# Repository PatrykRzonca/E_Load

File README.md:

# E_Load
This is a directory for E_Load project created in Kicad.

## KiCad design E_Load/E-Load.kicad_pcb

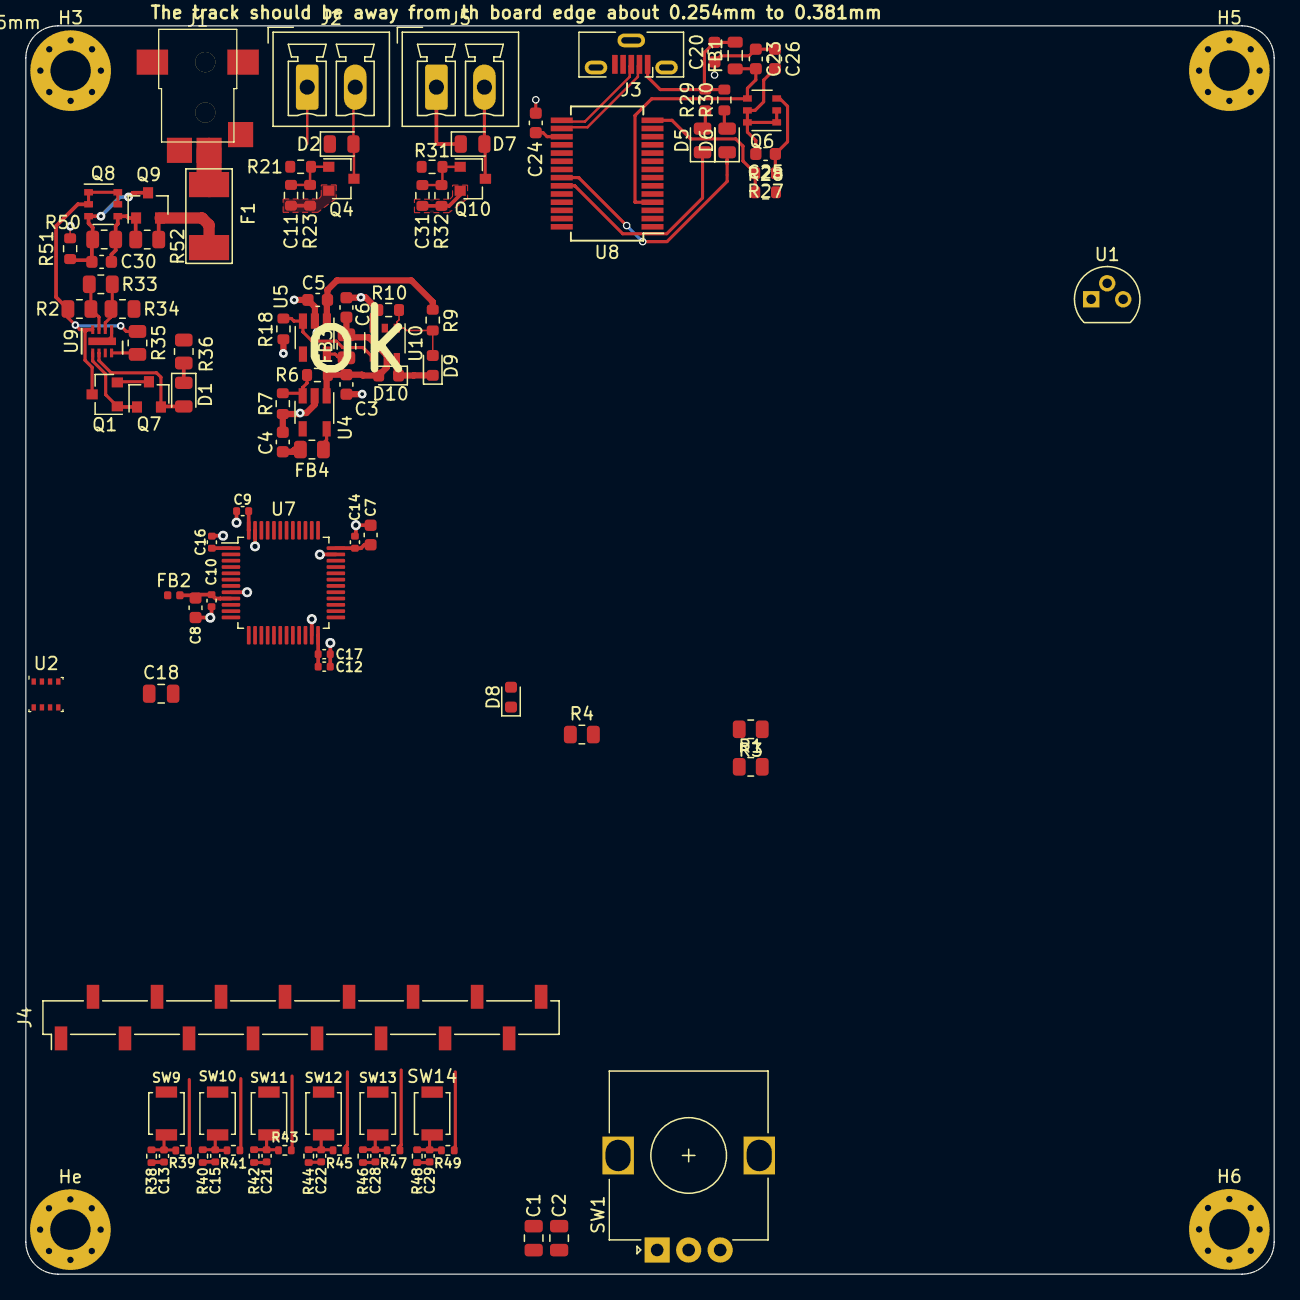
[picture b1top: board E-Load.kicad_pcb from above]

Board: 2 copper layers, 99.1 x 99.1 mm, 109 parts (0 on the bottom side), 49 nets.

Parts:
C1, C2, C18: 100n; C_0805_2012Metric
C3, C4, C5, C6, C30: C; C_0603_1608Metric
C7: 4u7; C_0603_1608Metric
C8: 1u; C_0603_1608Metric
C9, C10, C12, C14, C16, C17: 100n; C_0402_1005Metric
C11, C31: 100n; R_0603_1608Metric
C13, C15, C21, C22, C28, C29: C; C_0402_1005Metric
C20, C23, C24, C25, C26: 100n; C_0603_1608Metric
D1: LED; LED_0805_2012Metric
D2, D7: D; D_0805_2012Metric
D5: RED; LED_0805_2012Metric
D6: BLUE; LED_0805_2012Metric
D8, D9, D10: D_Schottky; D_0603_1608Metric
F1: Fuse; 0680-0500-12 BEL FUSE
FB1: Ferrite_Bead; L_0805_2012Metric
FB2: Ferrite_Bead_Small; L_0402_1005Metric
FB3, FB4: Ferrite_Bead_Small; R_0805_2012Metric
H3, H5, H6: MountingHole_Pad; MountingHole_3.2mm_M3_Pad_Via
He: MountingHole_Pad; MountingHole_3.2mm_M3_Pad_Via
J1: DC-8S_1.3mm_Pin; SMD DC SOCKETS DC-8S 1.3mm Pin
J2, J5: Screw_Terminal_01x02; PhoenixContact_MCV_1,5_2-G-3.81_1x02_P3.81mm_Vertical
J3: USB_B; USB_Micro-B_Molex-105133-0001
J4: Conn_01x16; PinSocket_1x16_P2.54mm_Vertical_SMD_Pin1Left
Q1, Q7: DMN24H3D5L; SOT-23
Q4, Q10: 2N7002E; SOT-23
Q6, Q8: PMN48XP; TSOP-6_1.65x3.05mm_P0.95mm
Q9: BC807; SOT-23
R1, R3, R4: 10k; R_0805_2012Metric
R2, R33, R34, R35, R36, R50, R52: R; R_0805_2012Metric
R6, R7, R18, R51: R; R_0603_1608Metric
R9, R10, R21, R23, R27, R28, R30, R31, R32: 10k; R_0603_1608Metric
R29: 10kΩ; R_0603_1608Metric
R38, R39, R40, R41, R42, R43, R44, R45, R46, R47, R48, R49: 10k; R_0402_1005Metric
SW1: Rotary_Encoder_Switch; RotaryEncoder_Alps_EC12E_Vertical_H20mm
SW9, SW10, SW11, SW12, SW13, SW14: SW_Push; SW_SPST_B3U-1000P
U1: DS18B20; TO-92
U2: BME280; Bosch_LGA-8_2.5x2.5mm_P0.65mm_ClockwisePinNumbering
U4: NCP718xSN330; TSOT-23-5
U5: NCP718xSN500; TSOT-23-5
U7: STM32F103C8Tx; LQFP-48_7x7mm_P0.5mm
U8: FT232RL; SSOP-28_5.3x10.2mm_P0.65mm
U9: LTC4365DDB; DFN-8-1EP_2x3mm_P0.5mm_EP0.61x2.2mm
U10: 74AHC1G86; TSOP-5_1.65x3.05mm_P0.95mm

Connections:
3V3_PS: C4.2, FB4.2, R1.2, R3.2, R4.2, U2.6, U2.8
5V_PS: C3.2, C6.2, D8.1, D10.2, FB3.2, J4.2, J4.15, R6.2, U1.3, U4.1
+3V3: C24.2, U8.17
+5V: C20.2, FB1.2, J3.1, R29.2, R30.2
/5V_USB: C25.2, C26.2, D8.2, Q6.1, Q6.2, Q6.5, Q6.6, U10.2
/CBUS3: R27.2, R28.1, U8.14
/D+: J3.3, U8.15
/D-: J3.2, U8.16
/ENC_BUTTON_A: C2.2, R3.1, SW1.A
/ENC_BUTTON_B: C1.2, R1.1, SW1.B
/LDO_5V_EN: R18.2, U5.3, U10.4
/~FAULT: U7.18, U9.7
GND: C1.1, C2.1, C3.1, C4.1, C5.1, C6.1, C7.1, C8.1, C9.1, C10.1, C11.1, C12.1, C13.2, C14.1, C15.2, C16.1, C17.1, C18.1, C20.1, C21.2, C22.2, C23.1, C24.1, C26.1, C28.2, C29.2, C31.1, H3.1, H5.1, H6.1, He.1, J1.2, J3.4, J3.5, J4.1, J4.16, Q4.2, Q10.2, R7.1, R10.1, R18.1, R23.2, R32.2, R34.1, R36.2, R38.1, R40.1, R42.1, R44.1, R46.2, R48.1, R51.1, SW1.C, U1.1, U2.1, U2.7, U4.2, U5.2, U7.8, U7.23, U7.35, U7.47, U8.7, U8.18, U8.21, U8.25, U8.26, U9.1, U9.9, U10.3
Main_PS: C5.2, D1.2, D2.1, D7.1, J2.1, J5.1, Q7.2, R9.2, U5.1, U9.6
unnamed: C11.2, Q4.1, R21.2, R23.1
unnamed: C13.1, R38.2, R39.1, SW9.1
unnamed: C15.1, R40.2, R41.1, SW10.1
unnamed: C18.2, U7.7
unnamed: C21.1, R42.2, R43.1, SW11.1
unnamed: C22.1, R44.2, R45.1, SW12.1
unnamed: C23.2, FB1.1, Q6.4, U8.4, U8.20
unnamed: C25.1, Q6.3, R27.1
unnamed: C28.1, R46.1, R47.1, SW13.1
unnamed: C29.1, R48.2, R49.1, SW14.1
unnamed: C30.1, Q8.3, Q9.3, R50.1, R51.2
unnamed: C30.2, Q8.4, Q9.1, R50.2, R52.2
unnamed: C31.2, Q10.1, R31.2, R32.1
unnamed: D1.1, R36.1
unnamed: D2.2, J2.2, Q4.3
unnamed: D5.1, U8.23
unnamed: D5.2, R29.1
unnamed: D6.1, U8.22
unnamed: D6.2, R30.1
unnamed: D7.2, J5.2, Q10.3
unnamed: D9.2, R9.1, R10.2, U10.1
unnamed: F1.1, Q9.2, R52.1
unnamed: F1.2, J1.1
unnamed: FB3.1, U5.5
unnamed: FB4.1, U4.5
unnamed: Q1.1, Q7.1, U9.5
unnamed: Q1.2, Q7.3
unnamed: Q1.3, Q8.1, Q8.2, Q8.5, Q8.6, R2.2, R35.2, U9.4
unnamed: R2.1, R33.2, U9.3
unnamed: R6.1, R7.2, U4.3
unnamed: R33.1, R34.2, U9.2
unnamed: R35.1, U9.8
VCC: D9.1, D10.1, U10.5
VDD: C7.2, C9.2, C12.2, C14.2, C16.2, C17.2, FB2.1, SW9.2, SW10.2, SW11.2, SW12.2, SW13.2, SW14.2, U7.1, U7.24, U7.36, U7.48
VDDA: C8.2, C10.2, FB2.2, U7.9

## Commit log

2020-12-03 Addin KiCad files fo E-load project
2020-12-28 It is first page of schematic responsible for charging
